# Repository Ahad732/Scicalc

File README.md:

# Scicalc

 Scicalc is a scientific calculator inspired by the TI 84 calculator. It features the rp2350a mcu with the RP Rm2 radio module for bluetooth and wifi connectivity which are essential in daily life. It has a 2 inch tft lcd display which had bright colors and has a in built rechargable battery. It supports 1.5A fast charging along with a modular architecture.  

 The firmware for this project can be found [here](https://github.com/Keyaan-07/scicalc-fw)
 
 # Features  

 - Features a large 2 inch color display for advanced calculations.  
 - A fast mcu for advanced calculations which is newer and faster.  
 - 128 mbit storage for firmware which can be updated for new features.  
 - Fully custom design and Open Source!  
 - Cheap to make and helps in evolving skills.  

# Images
The 3d model looks like this:  

The keycaps attach to the buttons in this manner. I had this idea after looking at bridges!  

CAD model can be found [here](https://cad.onshape.com/documents/84fe92d66eafc534d9523f7c/w/e5f687d44fa54d018b5fb56d/e/4c7f7c65e5851fcead59abe7)!! View the PCB Online [here on Kicanvas](https://kicanvas.org/?repo=https%3A%2F%2Fgithub.com%2FAhad732%2FScicalc%2Ftree%2Fmain%2FHardware)  

BOM
|Designator                                  |Footprint                              |Value                      |Quantity|Price|Link                                                                                 |
|--------------------------------------------|---------------------------------------|---------------------------|--------|-----|-------------------------------------------------------------------------------------|
|C1, C10, C11, C2, C3, C4, C5, C6, C7, C8, C9|402                                    |100n                       |100     |0.16 |https://www.lcsc.com/product-detail/C5137487.html                                    |
|C15, C16                                    |402                                    |15p                        |100     |0.1  |https://www.lcsc.com/product-detail/C5448872.html                                    |
|C17, C18                                    |402                                    |10u                        |20      |0.42 |https://www.lcsc.com/product-detail/C6119763.html                                    |
|C19                                         |402                                    |1u                         |50      |0.12 |https://www.lcsc.com/product-detail/C7393850.html                                    |
|D1-D50                                      |D_SOD-123                              |1N4148W                    |100     |0.65 |https://www.lcsc.com/product-detail/C5381435.html                                    |
|D53                                         |402                                    |Red                        |100     |0.67 |https://www.lcsc.com/product-image/C52675960.html                                    |
|D54                                         |402                                    |Green                      |100     |0.61 |https://www.lcsc.com/product-detail/C55072283.html                                   |
|J1                                          |USB_C_Receptacle_HCTL_HC-TYPE-C-16P-01A|USB_C_Receptacle_USB2.0_16P|10      |0.68 |https://www.lcsc.com/product-image/C7507405.html                                     |
|J2                                          |PinHeader_1x02_P2.54mm_Vertical        |Battery-2000 Mah           |1       |6.62 |https://robu.in/product/wly104050-2500mah-3-7v-single-cell-rechargeable-lipo-battery/|
|J3                                          |PinSocket_1x09_P2.54mm_Vertical        |Screen                     |1       |9.57 |https://robu.in/product/smartelex-2-inch-ips-tft-lcd-module/                         |
|L1                                          |603                                    |3.3u                       |50      |0.57 |https://www.lcsc.com/product-image/C411948.html                                      |
|R1, R2                                      |402                                    |27                         |100     |0.06 |https://www.lcsc.com/product-detail/C55098303.html                                   |
|R10, R5, R8                                 |402                                    |10K                        |100     |0.09 |https://www.lcsc.com/product-detail/C2759773.html                                    |
|R11                                         |402                                    |604                        |100     |0.08 |https://www.lcsc.com/product-detail/C49656019.html                                   |
|R3, R4                                      |402                                    |5.1K                       |100     |0.06 |https://www.lcsc.com/product-detail/C54920813.html                                   |
|R9                                          |402                                    |470                        |100     |0.06 |https://www.lcsc.com/product-detail/C54920802.html                                   |
|SW1-SW51                                    |SW_SPST_TS-1088-xR020                  |SW_Push                    |60      |3.03 |https://www.lcsc.com/product-detail/C720477.html                                     |
|U1                                          |QFN-60-1EP_7x7mm_P0.4mm_EP3.4x3.4mm    |RP2350A                    |3       |3.9  |https://www.lcsc.com/product-detail/C42411118.html                                   |
|U2                                          |SOT-23                                 |MCP1700x-330xxTT           |5       |0.55 |https://www.lcsc.com/product-detail/C41381676.html                                   |
|U3                                          |WSON-8-1EP_6x5mm_P1.27mm_EP3.4x4.3mm   |W25Q128JVP                 |3       |10.27|https://www.lcsc.com/product-detail/C190862.html                                     |
|U5                                          |rpi_rmc20452t                          |RM2                        |1       |7.05 |https://robu.in/product/raspberry-pi-radio-module-rmc20452t/                         |
|U6                                          |VQFN-16-1EP_3x3mm_P0.5mm_EP1.6x1.6mm   |BQ24075RGT                 |3       |3.24 |https://www.lcsc.com/product-detail/C15464.html                                      |
|Y1                                          |Crystal_SMD_3225-4Pin_3.2x2.5mm        |12 mhz                     |5       |0.59 |https://www.lcsc.com/product-detail/C46613546.html                                   |
|                                            |                                       |PCB + Stencil              |        |19.12|                                                                                     |
|                                            |                                       |Parts Shipping             |        |6.09 |                                                                                     |
|                                            |                                       |                           |Total   |74.36|                                                                                     |

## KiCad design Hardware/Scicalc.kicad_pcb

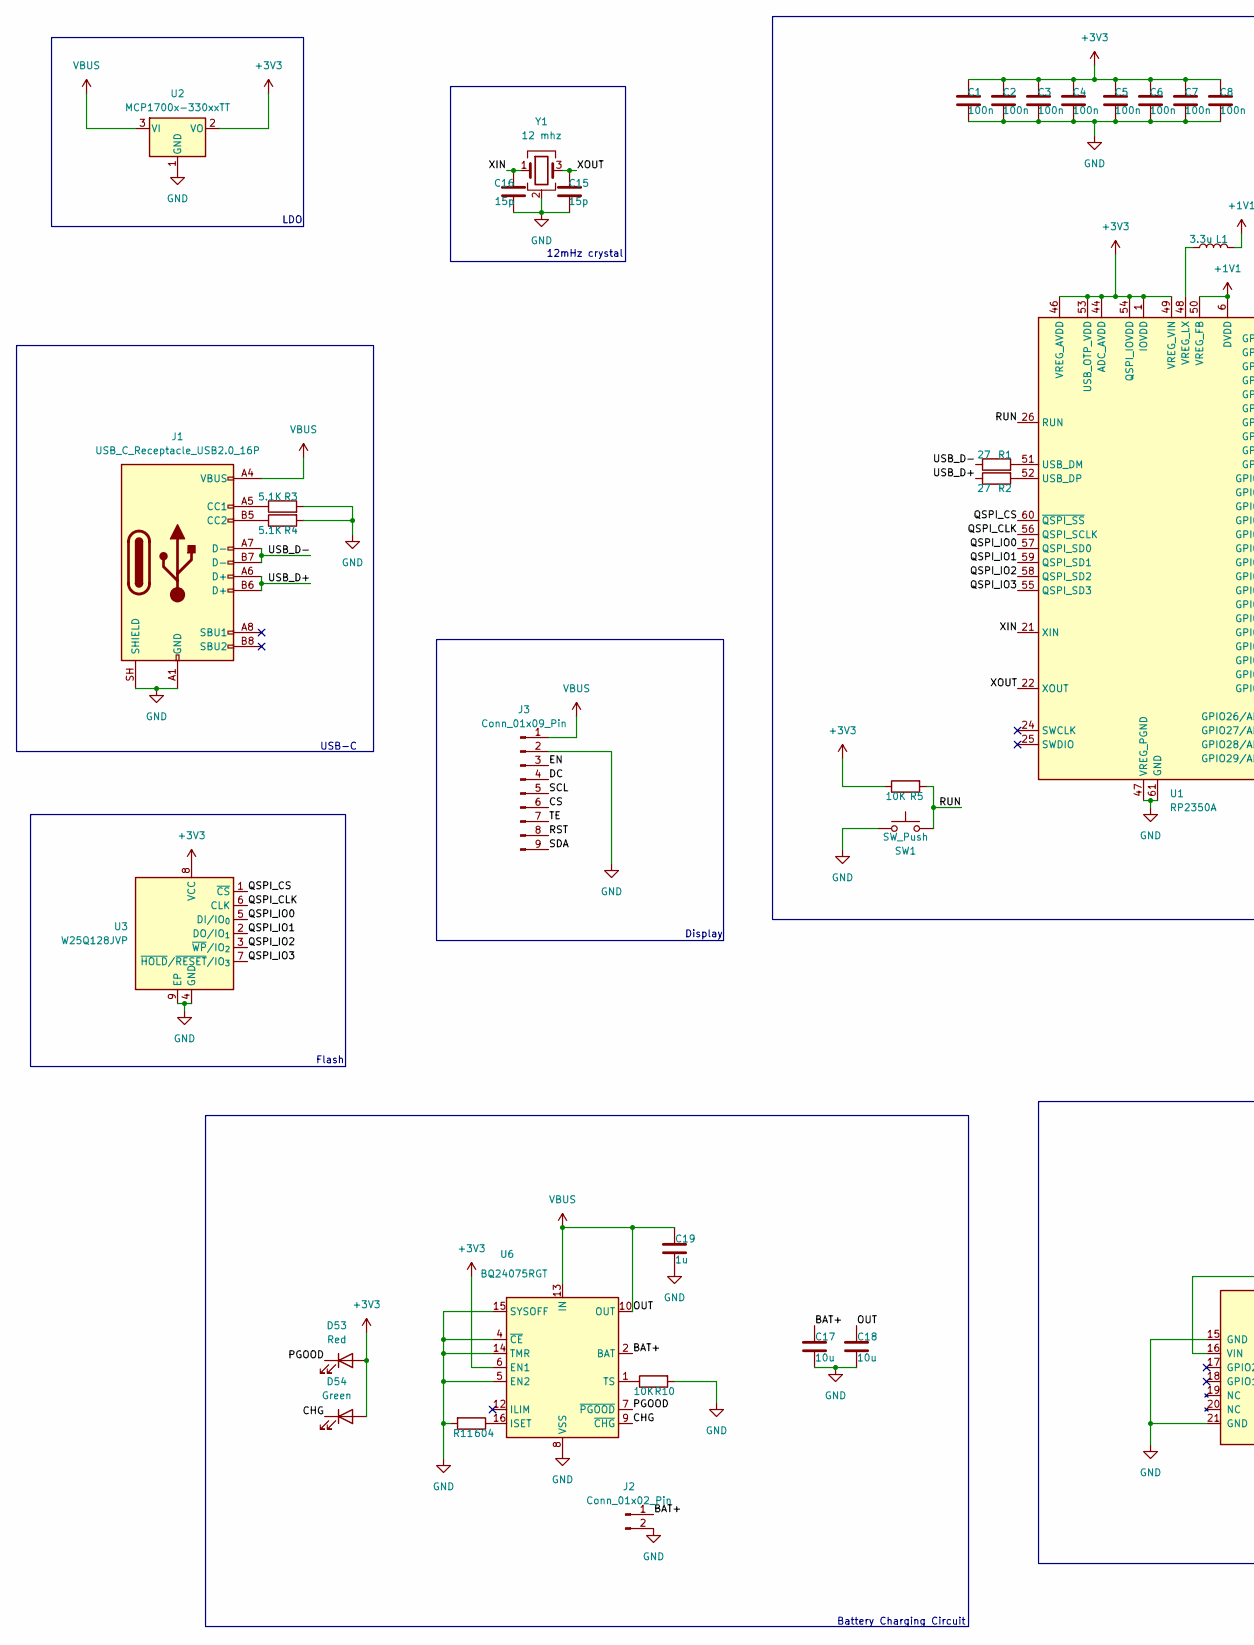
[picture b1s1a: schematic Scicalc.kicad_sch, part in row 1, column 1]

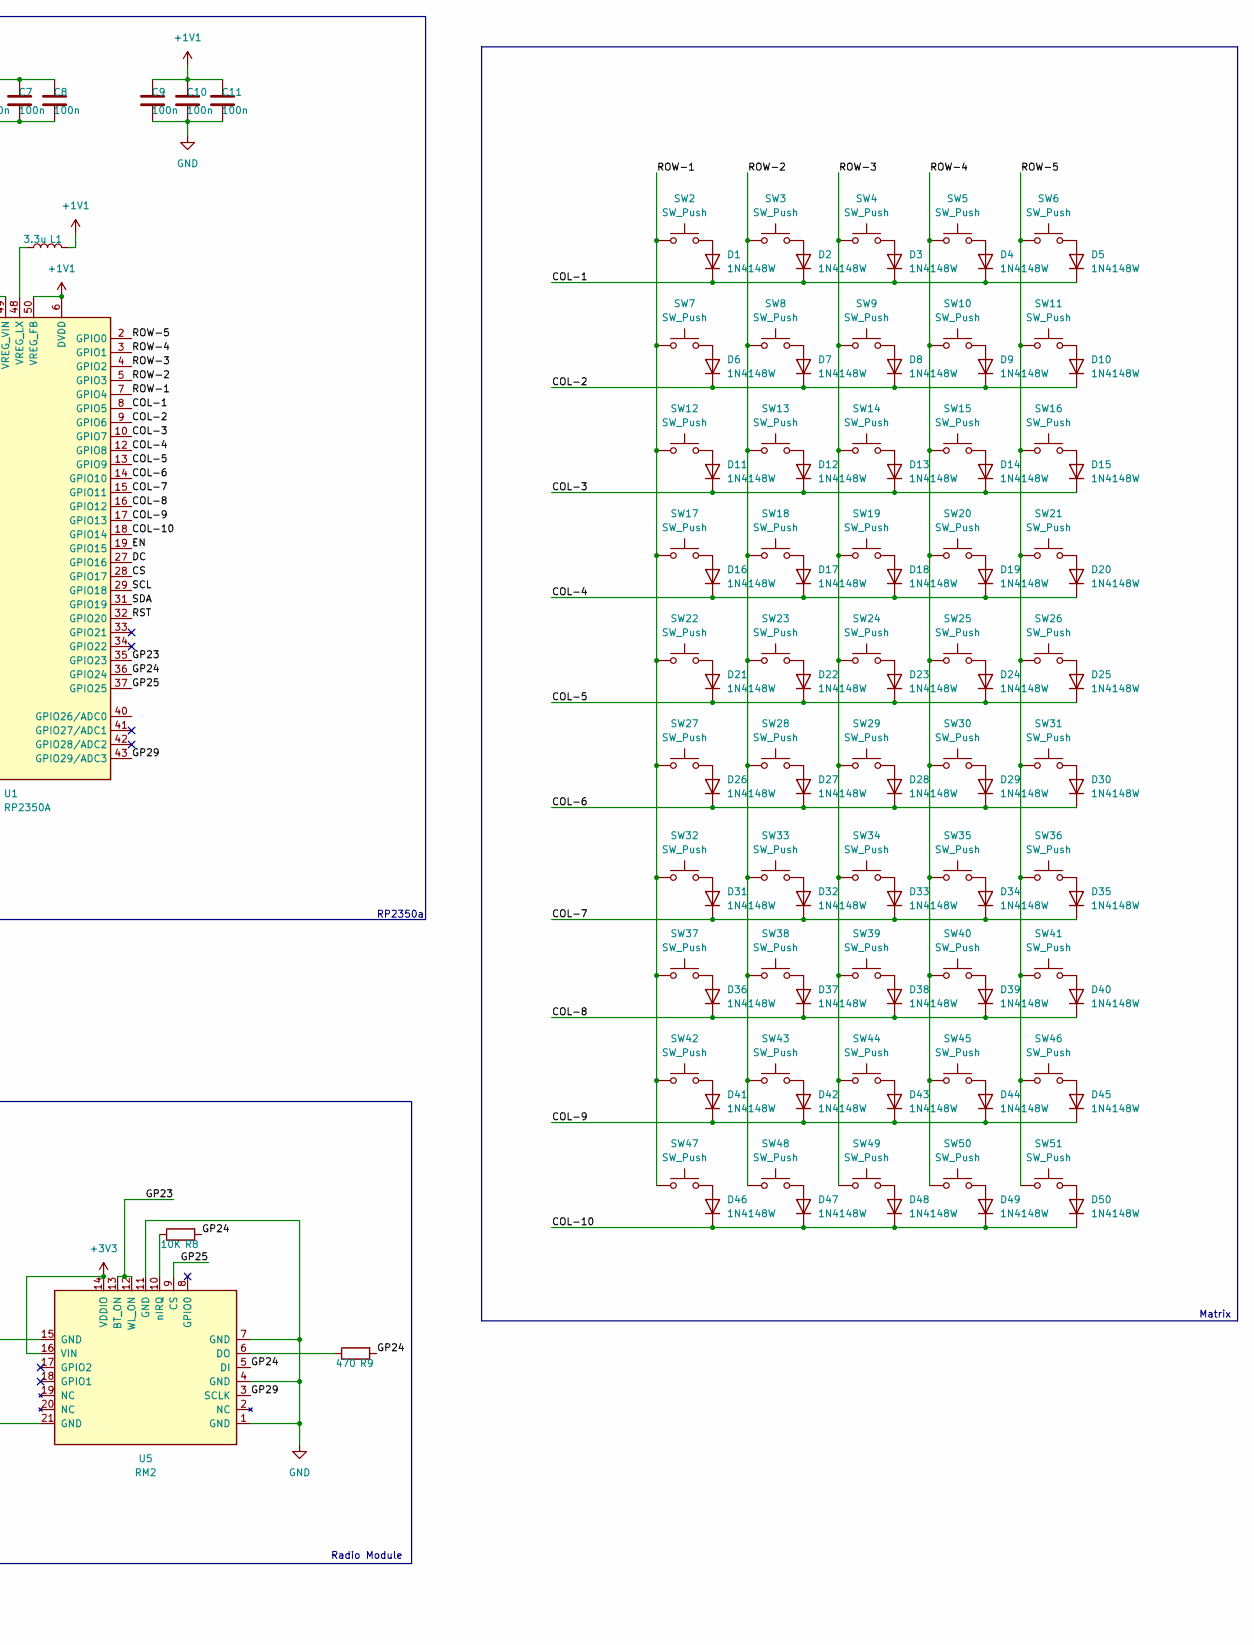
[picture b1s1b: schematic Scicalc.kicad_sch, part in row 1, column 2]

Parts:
C1, C2, C3, C4, C5, C6, C7, C8, C9, C10, C11: 100n; C_0402_1005Metric
C15, C16: 15p; C_0402_1005Metric
C17, C18: 10u; C_0402_1005Metric
C19: 1u; C_0402_1005Metric
D1, D2, D3, D4, D5, D6, D7, D8, D9, D10, D11, D12, D13, D14, D15, D16, D17, D18, D19, D20, D21, D22, D23, D24, D25, D26, D27, D28, D29, D30, D31, D32, D33, D34, D35, D36, D37, D38, D39, D40, D41, D42, D43, D44, D45, D46, D47, D48, D49, D50: 1N4148W; D_SOD-123
D53: Red; LED_0402_1005Metric
D54: Green; LED_0402_1005Metric
J1: USB_C_Receptacle_USB2.0_16P; USB_C_Receptacle_HCTL_HC-TYPE-C-16P-01A
J2: Conn_01x02_Pin; PinHeader_1x02_P2.54mm_Vertical
J3: Conn_01x09_Pin; PinSocket_1x09_P2.54mm_Vertical
L1: 3.3u; L_0805_2012Metric
R1, R2: 27; R_0402_1005Metric
R3, R4: 5.1K; R_0402_1005Metric
R5, R8, R10: 10K; R_0402_1005Metric
R9: 470; R_0402_1005Metric
R11: 604; R_0402_1005Metric
SW1, SW2, SW3, SW4, SW5, SW6, SW7, SW8, SW9, SW10, SW11, SW12, SW13, SW14, SW15, SW16, SW17, SW18, SW19, SW20, SW21, SW22, SW23, SW24, SW25, SW26, SW27, SW28, SW29, SW30, SW31, SW32, SW33, SW34, SW35, SW36, SW37, SW38, SW39, SW40, SW41, SW42, SW43, SW44, SW45, SW46, SW47, SW48, SW49, SW50, SW51: SW_Push; SW_SPST_TS-1088-xR020
U1: RP2350A; QFN-60-1EP_7x7mm_P0.4mm_EP3.4x3.4mm
U2: MCP1700x-330xxTT; SOT-23
U3: W25Q128JVP; WSON-8-1EP_6x5mm_P1.27mm_EP3.4x4.3mm
U5: RM2; rpi_rmc20452t
U6: BQ24075RGT; VQFN-16-1EP_3x3mm_P0.5mm_EP1.6x1.6mm
Y1: 12 mhz; Crystal_SMD_3225-4Pin_3.2x2.5mm

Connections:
+1V1: C9.1, C10.1, C11.1, L1.2, U1.6 (DVDD), U1.23 (DVDD), U1.39 (DVDD), U1.50 (VREG_FB)
+3V3: C1.1, C2.1, C3.1, C4.1, C5.1, C6.1, C7.1, C8.1, D53.2 (A), D54.2 (A), R5.1, U1.1 (IOVDD), U1.11 (IOVDD), U1.20 (IOVDD), U1.30 (IOVDD), U1.38 (IOVDD), U1.44 (ADC_AVDD), U1.45 (IOVDD), U1.46 (VREG_AVDD), U1.49 (VREG_VIN), U1.53 (USB_OTP_VDD), U1.54 (QSPI_IOVDD), U2.2 (VO), U3.8 (VCC), U5.14 (VDDIO), U5.16 (VIN), U6.6 (EN1)
/BAT+: C17.1, J2.1, U6.2 (BAT), U6.3 (BAT)
/CHG: D54.1 (K), U6.9 (~CHG)
/COL-1: D1.1 (K), D2.1 (K), D3.1 (K), D4.1 (K), D5.1 (K), U1.8 (GPIO5)
/COL-2: D6.1 (K), D7.1 (K), D8.1 (K), D9.1 (K), D10.1 (K), U1.9 (GPIO6)
/COL-3: D11.1 (K), D12.1 (K), D13.1 (K), D14.1 (K), D15.1 (K), U1.10 (GPIO7)
/COL-4: D16.1 (K), D17.1 (K), D18.1 (K), D19.1 (K), D20.1 (K), U1.12 (GPIO8)
/COL-5: D21.1 (K), D22.1 (K), D23.1 (K), D24.1 (K), D25.1 (K), U1.13 (GPIO9)
/COL-6: D26.1 (K), D27.1 (K), D28.1 (K), D29.1 (K), D30.1 (K), U1.14 (GPIO10)
/COL-7: D31.1 (K), D32.1 (K), D33.1 (K), D34.1 (K), D35.1 (K), U1.15 (GPIO11)
/COL-8: D36.1 (K), D37.1 (K), D38.1 (K), D39.1 (K), D40.1 (K), U1.16 (GPIO12)
/COL-9: D41.1 (K), D42.1 (K), D43.1 (K), D44.1 (K), D45.1 (K), U1.17 (GPIO13)
/COL-10: D46.1 (K), D47.1 (K), D48.1 (K), D49.1 (K), D50.1 (K), U1.18 (GPIO14)
/CS: J3.6, U1.28 (GPIO17)
/DC: J3.4, U1.27 (GPIO16)
/EN: J3.3, U1.19 (GPIO15)
/GP23: U1.35 (GPIO23), U5.12 (WL_ON), U5.13 (BT_ON)
/GP24: R8.2, R9.2, U1.36 (GPIO24), U5.5 (DI)
/GP25: U1.37 (GPIO25), U5.9 (CS)
/GP29: U1.43 (GPIO29/ADC3), U5.3 (SCLK)
/PGOOD: D53.1 (K), U6.7 (~PGOOD)
/QSPI_CLK: U1.56 (QSPI_SCLK), U3.6 (CLK)
/QSPI_CS: U1.60 (~QSPI_SS), U3.1 (~CS)
/QSPI_IO0: U1.57 (QSPI_SD0), U3.5 (DI/IO_{0})
/QSPI_IO1: U1.59 (QSPI_SD1), U3.2 (DO/IO_{1})
/QSPI_IO2: U1.58 (QSPI_SD2), U3.3 (~WP/IO_{2})
/QSPI_IO3: U1.55 (QSPI_SD3), U3.7 (~HOLD/~RESET/IO_{3})
/ROW-1: SW2.1, SW7.1, SW12.1, SW17.1, SW22.1, SW27.1, SW32.1, SW37.1, SW42.1, SW47.1, U1.7 (GPIO4)
/ROW-2: SW3.1, SW8.1, SW13.1, SW18.1, SW23.1, SW28.1, SW33.1, SW38.1, SW43.1, SW48.1, U1.5 (GPIO3)
/ROW-3: SW4.1, SW9.1, SW14.1, SW19.1, SW24.1, SW29.1, SW34.1, SW39.1, SW44.1, SW49.1, U1.4 (GPIO2)
/ROW-4: SW5.1, SW10.1, SW15.1, SW20.1, SW25.1, SW30.1, SW35.1, SW40.1, SW45.1, SW50.1, U1.3 (GPIO1)
/ROW-5: SW6.1, SW11.1, SW16.1, SW21.1, SW26.1, SW31.1, SW36.1, SW41.1, SW46.1, SW51.1, U1.2 (GPIO0)
/RST: J3.8, U1.32 (GPIO20)
/RUN: R5.2, SW1.2, U1.26 (RUN)
/SCL: J3.5, U1.29 (GPIO18)
/SDA: J3.9, U1.31 (GPIO19)
/TE: J3.7
/USB_D+: J1.A6 (D+), J1.B6 (D+), R2.1
/USB_D-: J1.A7 (D-), J1.B7 (D-), R1.1
/XIN: C16.1, U1.21 (XIN), Y1.1
/XOUT: C15.1, U1.22 (XOUT), Y1.3
GND: C1.2, C2.2, C3.2, C4.2, C5.2, C6.2, C7.2, C8.2, C9.2, C10.2, C11.2, C15.2, C16.2, C17.2, C18.2, C19.2, J1.A1 (GND), J1.A12 (GND), J1.B1 (GND), J1.B12 (GND), J1.SH (SHIELD), J2.2, J3.2, R3.2, R4.2, R10.2, R11.2, SW1.1, U1.47 (VREG_PGND), U1.61 (GND), U2.1 (GND), U3.4 (GND), U3.9 (EP), U5.1 (GND), U5.4 (GND), U5.7 (GND), U5.11 (GND), U5.15 (GND), U5.21 (GND), U6.4 (~CE), U6.5 (EN2), U6.8 (VSS), U6.14 (TMR), U6.15 (SYSOFF), U6.17 (VSS), Y1.2 (G), Y1.4 (G)
unnamed: D1.2 (A), SW2.2
unnamed: D2.2 (A), SW3.2
unnamed: D3.2 (A), SW4.2
unnamed: D4.2 (A), SW5.2
unnamed: D5.2 (A), SW6.2
unnamed: D6.2 (A), SW7.2
unnamed: D7.2 (A), SW8.2
unnamed: D8.2 (A), SW9.2
unnamed: D9.2 (A), SW10.2
unnamed: D10.2 (A), SW11.2
unnamed: D11.2 (A), SW12.2
unnamed: D12.2 (A), SW13.2
unnamed: D13.2 (A), SW14.2
unnamed: D14.2 (A), SW15.2
unnamed: D15.2 (A), SW16.2
unnamed: D16.2 (A), SW17.2
unnamed: D17.2 (A), SW18.2
unnamed: D18.2 (A), SW19.2
unnamed: D19.2 (A), SW20.2
unnamed: D20.2 (A), SW21.2
unnamed: D21.2 (A), SW22.2
unnamed: D22.2 (A), SW23.2
unnamed: D23.2 (A), SW24.2
unnamed: D24.2 (A), SW25.2
unnamed: D25.2 (A), SW26.2
unnamed: D26.2 (A), SW27.2
unnamed: D27.2 (A), SW28.2
unnamed: D28.2 (A), SW29.2
unnamed: D29.2 (A), SW30.2
unnamed: D30.2 (A), SW31.2
unnamed: D31.2 (A), SW32.2
unnamed: D32.2 (A), SW33.2
unnamed: D33.2 (A), SW34.2
unnamed: D34.2 (A), SW35.2
unnamed: D35.2 (A), SW36.2
unnamed: D36.2 (A), SW37.2
unnamed: D37.2 (A), SW38.2
unnamed: D38.2 (A), SW39.2
unnamed: D39.2 (A), SW40.2
unnamed: D40.2 (A), SW41.2
unnamed: D41.2 (A), SW42.2
unnamed: D42.2 (A), SW43.2
unnamed: D43.2 (A), SW44.2
unnamed: D44.2 (A), SW45.2
unnamed: D45.2 (A), SW46.2
unnamed: D46.2 (A), SW47.2
unnamed: D47.2 (A), SW48.2
unnamed: D48.2 (A), SW49.2
unnamed: D49.2 (A), SW50.2
unnamed: D50.2 (A), SW51.2
unnamed: J1.A5 (CC1), R3.1
unnamed: J1.B5 (CC2), R4.1
unnamed: R1.2, U1.51 (USB_DM)
unnamed: R2.2, U1.52 (USB_DP)
unnamed: L1.1, U1.48 (VREG_LX)
unnamed: R9.1, U5.6 (DO)
unnamed: R8.1, U5.10 (nIRQ)
unnamed: R11.1, U6.16 (ISET)
unnamed: R10.1, U6.1 (TS)
VBUS: C18.1, C19.1, J1.A4 (VBUS), J1.A9 (VBUS), J1.B4 (VBUS), J1.B9 (VBUS), J3.1, U2.3 (VI), U6.10 (OUT), U6.11 (OUT), U6.13 (IN)

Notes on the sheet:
Battery Charging Circuit
USB-C
RP2350a
Matrix
Display
Radio Module
12mHz crystal
Flash
LDO

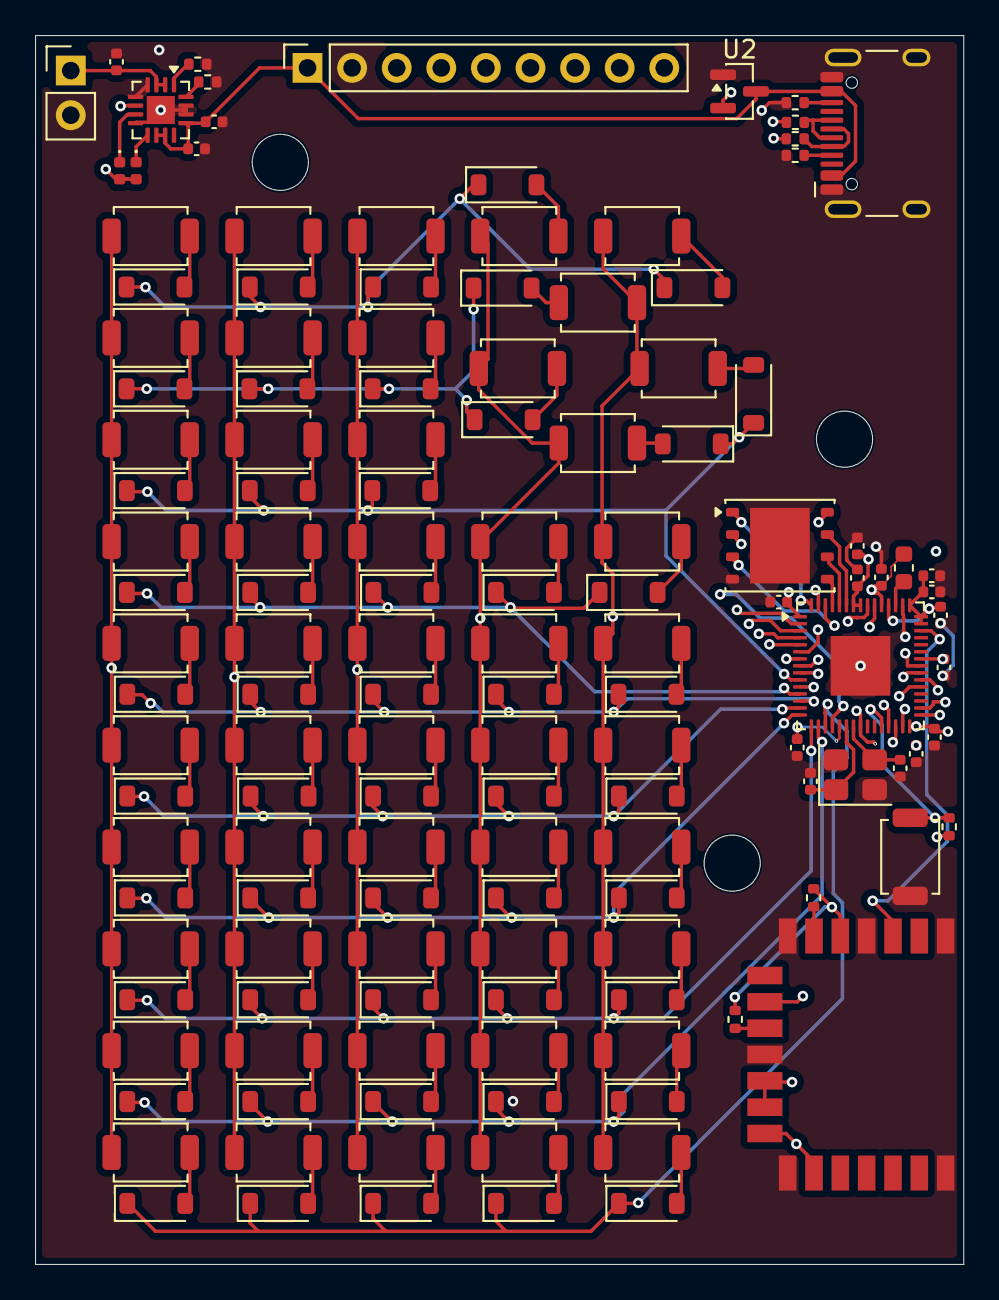
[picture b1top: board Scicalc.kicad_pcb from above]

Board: 4 copper layers, 52.9 x 70.0 mm, 138 parts (0 on the bottom side), 102 nets.

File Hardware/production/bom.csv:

Designator,Footprint,Quantity,Value,LCSC Part #
"C1, C10, C11, C2, C3, C4, C5, C6, C7, C8, C9",0402,11,100n,
"C15, C16",0402,2,15p,
"C17, C18",0402,2,10u,
C19,0402,1,1u,
"D1, D10, D11, D12, D13, D14, D15, D16, D17, D18, D19, D2, D20, D21, D22, D23, D24, D25, D26, D27, D28, D29, D3, D30, D31, D32, D33, D34, D35, D36, D37, D38, D39, D4, D40, D41, D42, D43, D44, D45, D46, D47, D48, D49, D5, D50, D6, D7, D8, D9",D_SOD-123,50,1N4148W,
D53,0402,1,Red,
D54,0402,1,Green,
J1,USB_C_Receptacle_HCTL_HC-TYPE-C-16P-01A,1,USB_C_Receptacle_USB2.0_16P,
J2,PinHeader_1x02_P2.54mm_Vertical,1,Conn_01x02_Pin,
J3,PinSocket_1x09_P2.54mm_Vertical,1,Conn_01x09_Pin,
L1,0603,1,3.3u,
"R1, R2",0402,2,27,
"R10, R5, R8",0402,3,10K,
R11,0402,1,604,
"R3, R4",0402,2,5.1K,
R9,0402,1,470,
"SW1, SW10, SW11, SW12, SW13, SW14, SW15, SW16, SW17, SW18, SW19, SW2, SW20, SW21, SW22, SW23, SW24, SW25, SW26, SW27, SW28, SW29, SW3, SW30, SW31, SW32, SW33, SW34, SW35, SW36, SW37, SW38, SW39, SW4, SW40, SW41, SW42, SW43, SW44, SW45, SW46, SW47, SW48, SW49, SW5, SW50, SW51, SW6, SW7, SW8, SW9",SW_SPST_TS-1088-xR020,51,SW_Push,
U1,QFN-60-1EP_7x7mm_P0.4mm_EP3.4x3.4mm,1,RP2350A,
U2,SOT-23,1,MCP1700x-330xxTT,
U3,WSON-8-1EP_6x5mm_P1.27mm_EP3.4x4.3mm,1,W25Q128JVP,
U5,rpi_rmc20452t,1,RM2,
U6,VQFN-16-1EP_3x3mm_P0.5mm_EP1.6x1.6mm,1,BQ24075RGT,
Y1,Crystal_SMD_3225-4Pin_3.2x2.5mm,1,12 mhz,
